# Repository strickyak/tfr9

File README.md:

# tfr9

The TFR/9 Single Board Computer for Hitachi 6309E or Motorola 6809E CPUs (TFR/901)

This represents one approach to mixing retro computers with modern
attachments: The CPU will be genuine retro, a 6809E or 6309E from the
era, but all the other parts are replaced by a Raspberry Pi Picos,
including the RAM and the E/Q clock generation.

The hope is to make very affordable Single Board Computers running
Nitros-9 Level 1 or 2 OS, since a 6309 is under $5, a Pi Pico is around $5.

(Another board taking this kind of modern-retro approach is the Olimex Neo6502
which sells for around 30 Euro.)

## TFR/905h

Finished, tested boards can be ordered (or soon can be ordered) from
https://computerconect.com/collections/coco-hardware

Here is the Hardware Reference Manual:
https://github.com/strickyak/tfr9/wiki/TFR-905-Hardware-Reference

Here is the latest software:
https://github.com/strickyak/tfr9/tree/main/v3

Here are the Kicad design files, and Gerbers and CPL and BOM for
[JLCPCB](https://jlcpcb.com/) :
https://github.com/strickyak/tfr9/tree/main/tfr905h

It works best with a
[Hitachi HD63C09EP](https://www.ebay.com/itm/375885991013) and a
[Pi Pico 2](https://www.digikey.com/en/products/detail/raspberry-pi/SC1631/24627136)
(and those links are where I got my parts from).

The design goals of the 905h were
 
* Cheap. Two layer, 100mm x 100mm, common parts.

* Works with all Pi Picos {1, 1w, 2, 2w}.

* Uses only 12 GPIO pins, from 0 to 11.

* That leaves plenty of GPIO lines free for audio, video,
interfacing, experimentation ... including all 8 HSTX (high
speed transmit) pins.

* All 40 pins on the 6309 and all 40 pins on the Pi Pico
can have headers attached, for easy interfacing.

* Powered and controlled over USB, by a program 
that runs on any modern PC (Windows, Mac, Linux, Pi).

* Anti-goals: Maybe not the fastest or the simplest
(but it's fast enough and simple enough).

## TFR/903 (obsolete)

This board should work with either 6809E or 6309E, but hereafter we'll
just call it the 6309, but we probably mean a Hitachi 63C09E.  The E is
important -- the CPU must be externally clocked.

We're starting with one Pico in the first prototype, but we might
add more:

* The first Pico is the controller.
  It provides clocks and simulates RAM (hopefully with MMU)
  and a terminal device.  Probably also disk and ethernet.

* A second Pico can generate video output.  This use of a Pico
  has been demonstrated several times, with VGA or DVI output,
  and even with an "HDMI connector".

* A third Pico could be a Pico W which does wifi internet.

## TFR/901 (2024-07-13) (obsolete)

The TFR/901 is the first prototype for the TFR/9 architecture.

It contains slots for a Hitachi 63C09E and one Raspberry Pi Pico, and just
enough multiplexing, latching, and voltage level shifting to connect them.

The hope is that the Pico can provide all the RAM and IO facilities
needed for the 6309/6809 CPU.  It also provides the E and Q clocks,
and there are connections for all inputs and outputs of the CPU chip.

Since this is for prototyping, there are optional header pins for all
interesting signals, and through-hole DIPs are used for all the chips.
There should be ample room to bodge stuff, if mistakes were made.

### First Pico

The first Pi Pico is the controller.  It has the ability to completely
control the 6309 CPU, as if the CPU lives suspended in the matrix.
And yet the 6309, and it alone, will do all the things you expect the
CPU to do.  It is not emulated or simulated, just controlled.

### First Pico Pins

GPIO pins G0 to G15 are a general purpose bidirectional bus.  What is
on this bus will depend on which Y mode is chosen, below.

GPIO pins 16 and 17 are output for the E and Q clock signals to the CPU,
These can be slowed down or sped up at the will of the Pi Pico.

G18, G19, and G20 are outputs to a 74138 3-to-8 decoder, which chooses
one of 8 modes, named Y0 to Y7.

Y0 does nothing.

Y1 maps CPU output Adddress lines A0-A15 to GPIO inputs G0 to G15.

Y2 maps CPU output Data lines D0-D7 to GPIO inputs G0 to G7, and also
various output signals R/W, AVMA, LIC, BUSY, BA, BS...  to GPIO inputs
in the range G8 to G15.

Y3 maps GPIO outputs G0 to G7 to CPU inputs D0-D7.

Y4 latches signals on G8 to G15 to various CPU inputs like RESET, HALT,
NMI, IRQ, FIRQ.   These are "slow" inputs that typically last more than
one CPU cycle, so they are latched, unlike the other signals above.

Y5, Y6, and Y7 will be trigger inputs to the second, third, etc, Pi
Picos, to send them data or receive data from them, over the G0 to G15
general bus.

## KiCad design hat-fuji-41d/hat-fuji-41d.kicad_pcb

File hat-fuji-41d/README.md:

# FujiNet Hat 41d

Works with Centipede 32z and the TFR/911h,
to provide FujiNet access.

Contains Bill Athing's fixes for the 40c,
and nary little more.

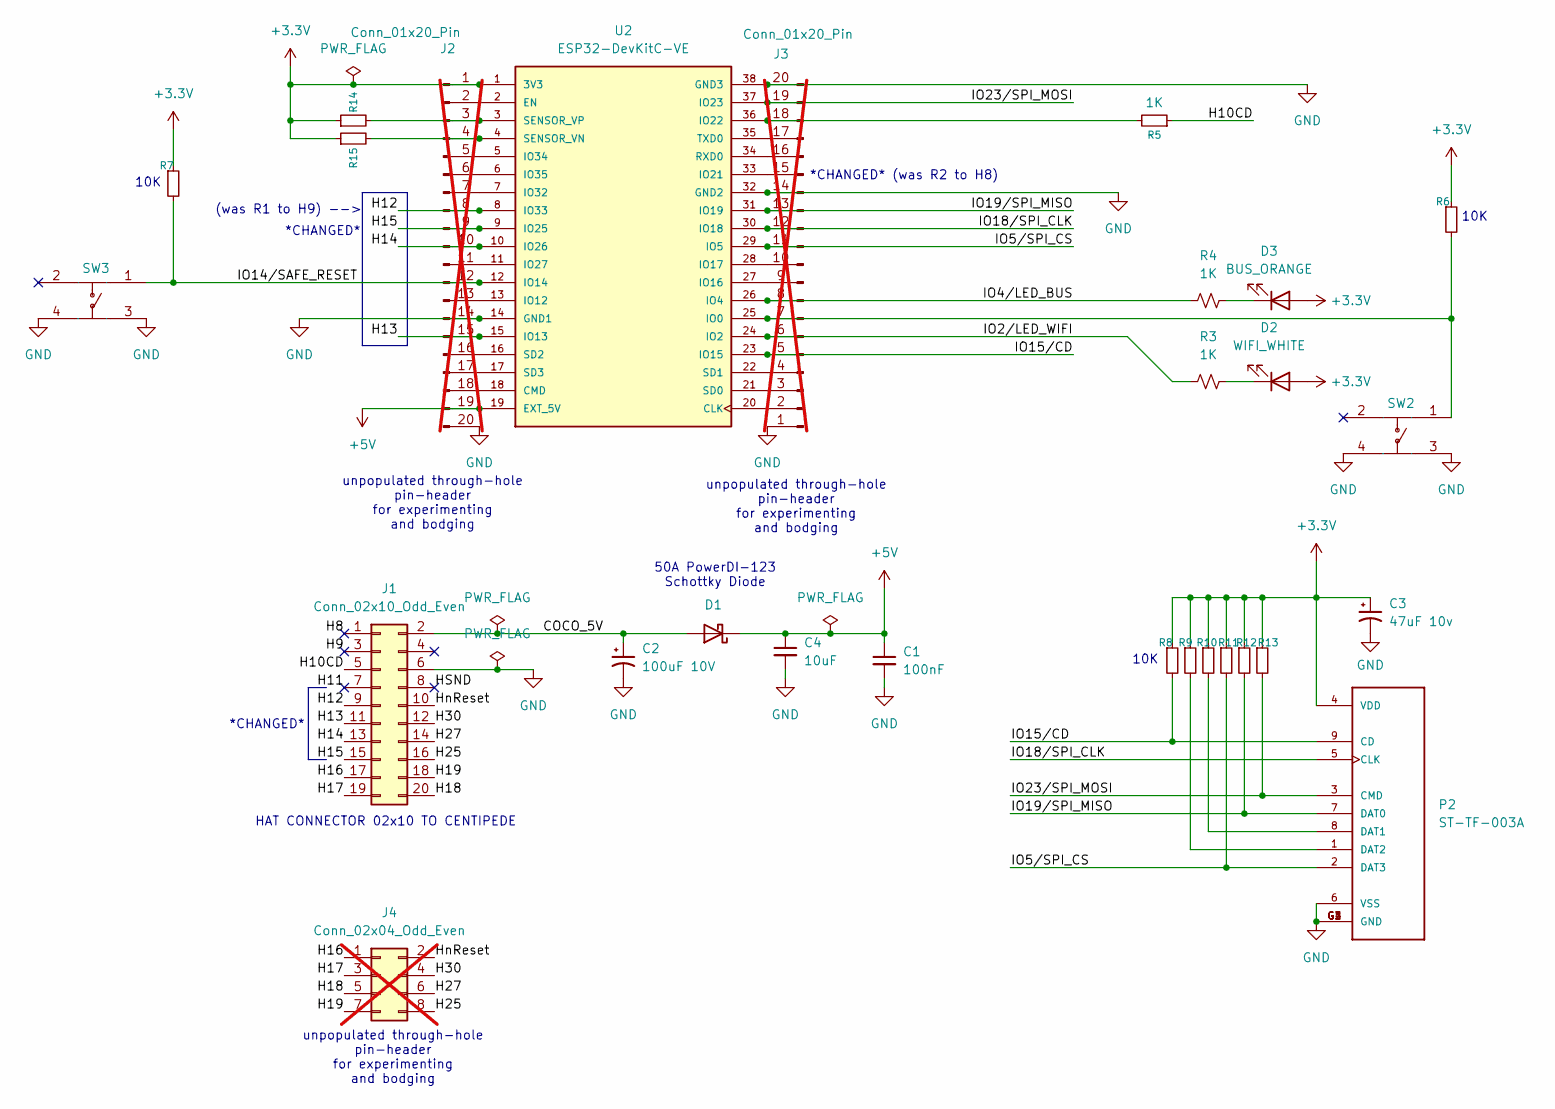
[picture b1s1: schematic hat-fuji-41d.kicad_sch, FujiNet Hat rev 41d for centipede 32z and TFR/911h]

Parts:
C1: 100nF; C_0402_1005Metric
C2: 100uF 10V; C_1206_3216Metric
C3: 47uF 10v; C_0805_2012Metric
C4: 10uF; C_0603_1608Metric
D1: 50A PowerDI-123 Schottky Diode; D_PowerDI-123
D2: WIFI_WHITE; LED_0603_1608Metric
D3: BUS_ORANGE; LED_0603_1608Metric
J1: Conn_02x10_Odd_Even; PinHeader_2x10_P2.54mm_Vertical_SMD
J2, J3: Conn_01x20_Pin; PinHeader_1x20_P2.54mm_Vertical; not fitted
J4: Conn_02x04_Odd_Even; PinHeader_2x04_P2.54mm_Vertical; not fitted
P2: ST-TF-003A; SUNTECH_ST-TF-003A
R3, R4, R5: 1K; R_0603_1608Metric
R6, R7, R8, R9, R10, R11, R12, R13, R14, R15: R_Small; R_0603_1608Metric
SW2, SW3: K2-1808SN-A4SW-01; KEY-SMD_4P-L4.2-W3.2-P2.20-LS5.1-TL; Manufacturer Part K2-1808SN-A4SW-01; LCSC Part Name 4.2mm*3.25mm
U2: ESP32-DevKitC-VE; MODULE_ESP32-DEVKITC-32U; PARTREV N/A

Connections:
+3.3V: C3.1, D2.2 (A), D3.2 (A), J2.1, P2.4 (VDD), R6.1, R7.1, R8.1, R9.1, R10.1, R11.1, R12.1, R13.1, R14.1, R15.1, U2.1 (3V3)
+5V: C1.1, C4.1, D1.1 (K), J2.19, U2.19 (EXT_5V)
/COCO_5V: C2.1, D1.2 (A), J1.2
/H8: J1.1
/H9: J1.3
/H10CD: J1.5, R5.1
/H11: J1.7
/H12: J1.9, J2.8, U2.8 (IO33)
/H13: J1.11, J2.15, U2.15 (IO13)
/H14: J1.13, J2.10, U2.10 (IO26)
/H15: J1.15, J2.9, U2.9 (IO25)
/H16: J1.17, J4.1
/H17: J1.19, J4.3
/H18: J1.20, J4.5
/H19: J1.18, J4.7
/H25: J1.16, J4.8
/H27: J1.14, J4.6
/H30: J1.12, J4.4
/HSND: J1.8
/HnReset: J1.10, J4.2
/IO2/LED_WIFI: J3.6, R3.2, U2.24 (IO2)
/IO4/LED_BUS: J3.8, R4.2, U2.26 (IO4)
/IO5/SPI_CS: J3.11, P2.2 (DAT3), R11.2, U2.29 (IO5)
/IO14/SAFE_RESET: J2.12, R7.2, SW3.1, U2.12 (IO14)
/IO15/CD: J3.5, P2.9 (CD), R8.2, U2.23 (IO15)
/IO18/SPI_CLK: J3.12, P2.5 (CLK), U2.30 (IO18)
/IO19/SPI_MISO: J3.13, P2.7 (DAT0), R12.2, U2.31 (IO19)
/IO23/SPI_MOSI: J3.19, P2.3 (CMD), R13.2, U2.37 (IO23)
GND: C1.2, C2.2, C3.2, C4.2, J1.6, J2.14, J2.20, J3.1, J3.14, J3.20, P2.6 (VSS), P2.G1 (GND), P2.G2 (GND), P2.G3 (GND), P2.G4 (GND), SW2.3, SW2.4, SW3.3, SW3.4, U2.14 (GND1), U2.32 (GND2), U2.38 (GND3)
unnamed: D2.1 (K), R3.1
unnamed: D3.1 (K), R4.1
unnamed: J2.2, U2.2 (EN)
unnamed: J2.3, R14.2, U2.3 (SENSOR_VP)
unnamed: J2.4, R15.2, U2.4 (SENSOR_VN)
unnamed: J2.5, U2.5 (IO34)
unnamed: J2.6, U2.6 (IO35)
unnamed: J2.7, U2.7 (IO32)
unnamed: J2.11, U2.11 (IO27)
unnamed: J2.13, U2.13 (IO12)
unnamed: J2.16, U2.16 (SD2)
unnamed: J2.17, U2.17 (SD3)
unnamed: J2.18, U2.18 (CMD)
unnamed: J3.2, U2.20 (CLK)
unnamed: J3.3, U2.21 (SD0)
unnamed: J3.4, U2.22 (SD1)
unnamed: J3.7, R6.2, SW2.1, U2.25 (IO0)
unnamed: J3.9, U2.27 (IO16)
unnamed: J3.10, U2.28 (IO17)
unnamed: J3.15, U2.33 (IO21)
unnamed: J3.16, U2.34 (RXD0)
unnamed: J3.17, U2.35 (TXD0)
unnamed: J3.18, R5.2, U2.36 (IO22)
unnamed: P2.8 (DAT1), R10.2
unnamed: P2.1 (DAT2), R9.2

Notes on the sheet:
50A PowerDI-123 Schottky Diode
10K
unpopulated through-hole pin-header for experimenting and bodging
*CHANGED*
HAT CONNECTOR 02x10 TO CENTIPEDE
*CHANGED* (was R2 to H8)
(was R1 to H9) -->

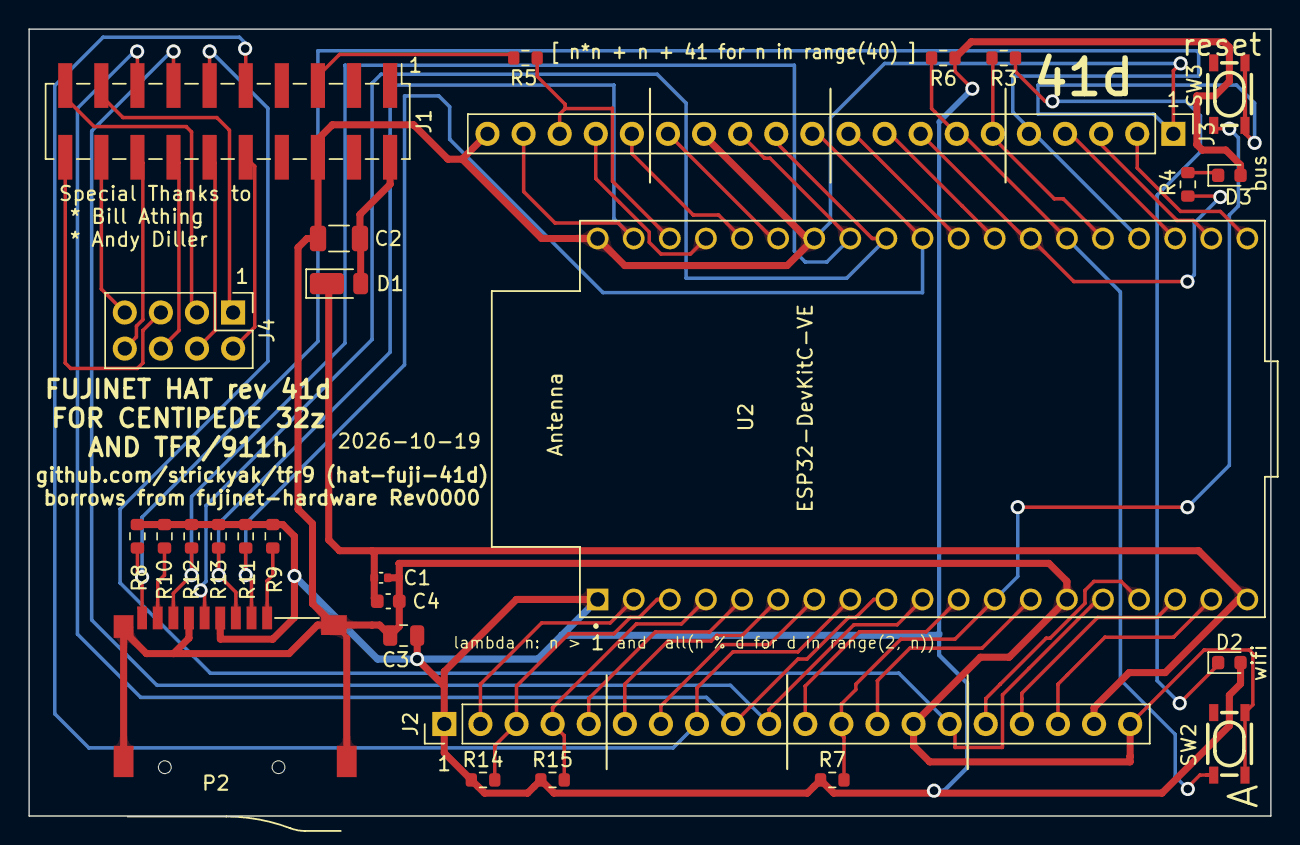
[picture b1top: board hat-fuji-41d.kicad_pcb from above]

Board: 2 copper layers, 87.4 x 55.4 mm, 28 parts (0 on the bottom side), 50 nets.

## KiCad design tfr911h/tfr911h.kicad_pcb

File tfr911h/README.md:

# RP2350B-Dev-Board

This is an RP2350B Dev board that breaks out all 48 GPIO pins.

It follows the original footprint of the RP2040 dev board, but adds 10 pins on each side.

It is not pin compatible with the original RP2040, though a version that shares the same pinout, at least for the first 20 pins on each side would be interesting.

Pinout:

```
1	GPIO0	        60	VBUS
2	GPIO1	        59	VSYS
3	GPIO2	        58	GND
4	GPIO3	        57	3v3
5	GPIO4	        56	3v3_EN
6	GPIO5	        55	ADC_VREF
7	GPIO6	        54	GND
8	GPIO7	        53	GPIO47/ADC7
9	GPIO8	        52	GPIO46/ADC6
10	GPIO9	        51	GPIO45/ADC5
11	GND	            50	GPIO44/ADC4
12	GPIO10	        49	GND
13	GPIO11	        48	GPIO43/ADC3
14	GPIO12	        47	GPIO42/ADC2
15	GPIO13	        46	GPIO41/ADC1
16	GPIO14	        45	GPIO40/ADC0
17	GPIO15	        44	GPIO39
18	GPIO16	        43	GPIO38
19	GPIO17	        42	GPIO37
20	GPIO18	        41	GPIO36
21	GPIO19	        40	GPIO35
22	GND	            39	GND
23	GPIO20	        38	GPIO34
24	GPIO21	        37	GPIO33
25	GPIO22	        36	GPIO32
26	GPIO23	        35	GPIO31
27	GPIO24	        34	GPIO30
28	GPIO25	        33	GPIO29
29	GPIO26	        32	GPIO28
30	GPIO27	        31	RUN
```

## Production files for JLCPCB

The production files for JLCPCB are in the 'production' directory.

RP2350_Dev_board.zip is the zipped Gerber files.

bom.csv and positions.csv are the Bill of materials and placements files respectively.

These were produced with the 'Fabrication Toolkit' plugin, which you will need to install if you need to regenerate them.

## Source Designs

Thie design borrows from https://pro.easyeda.com/editor#id=a0a21c97b13d436db5579fc2a8b1625d, which is an RP2350A design. I adapted it for the RP2350B, but it shares most of the schematic, if not the PCB layout.

I also looked at the RP2350B reference designs available here: https://datasheets.raspberrypi.com/rp2350/Minimal-KiCAD.zip

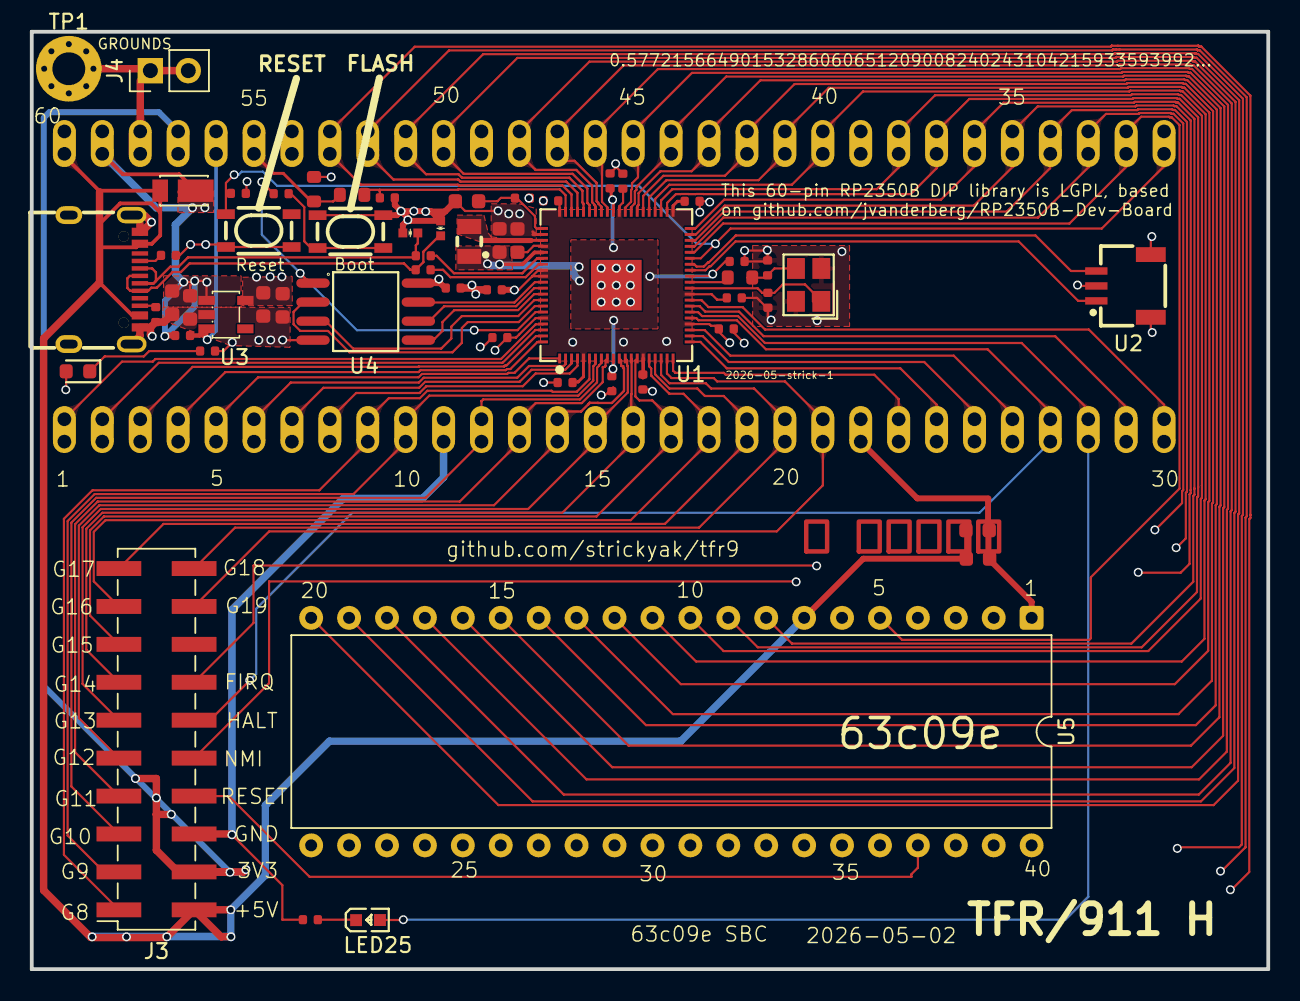
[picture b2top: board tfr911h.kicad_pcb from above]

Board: 4 copper layers, 82.8 x 62.8 mm, 116 parts (0 on the bottom side), 79 nets.

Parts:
3V3_EN1, 3V31: Castellated Pad
ADC_VREF1: Castellated Pad
Boot1: K2-1808SN-A4SW-01; KEY-SMD_4P-L4.2-W3.2-P2.20-LS5.1-TL
C1, C2, C3, C4, C5, C6, C7, C8, C9, C13, C14, C15, C16, C36: 100nF; C_0402
C10, C11, C12: 4.7uF; C_0603
C17, C18: 15pF; C_0402
C19: 4.7uF; C_0402
C20, C37, C40: 10uF; C_0603
C21, C38, C39: 100nF; C_0603
D1: POWERDI-123_L2.8-W1.8-LS3.7-RD
D2, D3: RCLAMP0521P.TCT-MS; D0402-BI
GND1, GND2, GND3, GND4, GND4#2, GND6: Castellated Pad
GPI10: Castellated Pad
GPIO0, GPIO1, GPIO1#2, GPIO1#3, GPIO1#4, GPIO1#5, GPIO1#6, GPIO1#7, GPIO1#8, GPIO2, GPIO3, GPIO4, GPIO5, GPIO7, GPIO8, GPIO11, GPIO12, GPIO13, GPIO15, GPIO16, GPIO17, GPIO18, GPIO19, GPIO21, GPIO21#2, GPIO22, GPIO24, GPIO25, GPIO26, GPIO27, GPIO28, GPIO29, GPIO30, GPIO32, GPIO34, GPIO35, GPIO36, GPIO37, GPIO38, GPIO39, GPIO40, GPIO41, GPIO42, GPIO43, GPIO44, GPIO45, GPIO46: Castellated Pad
J3: Conn_02x10_Odd_Even; PinSocket_2x10_P2.54mm_Vertical_SMD
J4: Conn_01x02; PinHeader_1x02_P2.54mm_Vertical
L1: IND-SMD_L2.0-W1.6_AOTA-B201610S3R3-101-T
LED25: Red; LED0603-RD_RED
PWR_LED1: Red; D_0603
R1, R4: 5.1kΩ; R_0402
R2, R3, R6: 33Ω; R_0402
R5: 1kΩ; R_0402
R7: 1Ω; R_0603
R8: 200Ω; R_0603
R9: 5kΩ; R_0402
R11: 100kΩ; R_0402
R12: 2kΩ; R_0402
R28: 1kΩ; R_0603
RUN1: Castellated Pad
Reset1: K2-1808SN-A4SW-01; KEY-SMD_4P-L4.2-W3.2-P2.20-LS5.1-TL
TP1: TestPoint_Alt; MountingHole_2.2mm_M2_Pad_Via
U1: QFN-80_L10.0-W10.0-P0.40-TL-EP3.4
U2: HC-1.0-3PWT; CONN-SMD_3P-P1.0-HC-1.0-3PWT
U3: SOT-23-5_L3.0-W1.7-P0.95-LS2.8-BR
U4: W25Q128; SOIC-8_L5.3-W5.3-P1.27-LS8.0-BL
U5: MC6809E; DIP-40_W15.24mm
USB1: USB-C-SMD_TYPE-C-6PIN-2MD-073
VBUS1: Castellated Pad
VSYS1: Castellated Pad
X1: CRYSTAL-SMD_4P-L3.2-W2.5-BL

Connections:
1V1: C2.1, C5.1, C10.2, C13.2, L1.2, U1.10 (DVDD), U1.32 (DVDD), U1.51 (DVDD), U1.65 (VREG_FB)
3V3: 3V31.57, C1.1, C3.1, C4.1, C6.1, C7.1, C8.2, C9.2, C12.2, C14.2, C16.2, C36.2, C38.1, C40.1, J3.4, PWR_LED1.2, R6.1, R8.2, U1.5 (IOVDD), U1.15 (IOVDD), U1.24 (IOVDD), U1.29 (IOVDD), U1.41 (IOVDD), U1.50 (IOVDD), U1.60 (IOVDD), U1.64 (VREG_VIN), U1.68 (USB_OTP_VDD), U1.69 (QSPI_IOVDD), U1.76 (IOVDD), U3.5 (VOUT), U4.8 (VCC)
3V3_EN: 3V3_EN1.56, R11.2, U3.3 (CE)
/VREG_LX: L1.1, U1.63 (VREG_LX)
ADC_VREF: ADC_VREF1.55, R7.2, R8.1
GND: Boot1.3, Boot1.4, C1.2, C2.2, C3.2, C4.2, C5.2, C6.2, C7.2, C8.1, C9.1, C10.1, C11.1, C12.1, C13.1, C14.1, C15.1, C16.1, C17.2, C18.1, C19.2, C20.2, C21.2, C36.1, C37.2, C38.2, C39.2, C40.2, D2.1, D3.1, GND2.22, GND3.39, GND4.49, GND4#2.54, GND6.58, GPI10.11, J3.6, J4.1, J4.2, R1.1, R4.1, R9.2, R12.2, Reset1.3, Reset1.4, TP1.1, U1.62 (VREG_PGND), U1.81 (GND), U2.2, U2.4, U2.5, U3.2 (VSS), U4.4 (GND), U5.1 (VSS), U5.39 (TSC), USB1.1 (GND), USB1.12 (GND), USB1.13 (SHELL), USB1.14 (SHELL), X1.2 (GND), X1.4 (GND)
GPIO0: GPIO0.1, U1.77 (GPIO0), U5.31 (D0)
GPIO1: GPIO1#2.2, U1.78 (GPIO1), U5.30 (D1)
GPIO2: GPIO2.3, U1.79 (GPIO2), U5.29 (D2)
GPIO3: GPIO3.4, U1.80 (GPIO3), U5.28 (D3)
GPIO4: GPIO4.5, U1.1 (GPIO4), U5.27 (D4)
GPIO5: GPIO5.6, U1.2 (GPIO5), U5.26 (D5)
GPIO6: GPIO1#8.7, U1.3 (GPIO6), U5.25 (D6)
GPIO7: GPIO7.8, U1.4 (GPIO7), U5.24 (D7)
GPIO8: GPIO8.9, J3.1, U1.6 (GPIO8)
GPIO9: GPIO1#7.10, J3.3, U1.7 (GPIO9)
GPIO10: GND1.12, J3.5, U1.8 (GPIO10)
GPIO11: GPIO11.13, J3.7, U1.9 (GPIO11)
GPIO12: GPIO12.14, J3.9, U1.11 (GPIO12)
GPIO13: GPIO13.15, J3.11, U1.12 (GPIO13)
GPIO14: GPIO1#6.16, J3.13, U1.13 (GPIO14)
GPIO15: GPIO15.17, J3.15, U1.14 (GPIO15)
GPIO16: GPIO16.18, J3.17, U1.16 (GPIO16)
GPIO17: GPIO17.19, J3.19, U1.17 (GPIO17)
GPIO18: GPIO18.20, J3.20, U1.18 (GPIO18)
GPIO19: GPIO19.21, J3.18, U1.19 (GPIO19)
GPIO20: GPIO21.23, J3.8, U1.20 (GPIO20), U5.37 (~RESET)
GPIO21: GPIO21#2.24, J3.10, U1.21 (GPIO21), U5.2 (~NMI)
GPIO22: GPIO22.25, U1.22 (GPIO22), U5.3 (~IRQ)
GPIO23: GPIO1#5.26, J3.14, U1.23 (GPIO23), U5.4 (~FIRQ)
GPIO24: GPIO24.27, J3.12, U1.25 (GPIO24), U5.40 (~HALT)
GPIO25: GPIO25.28, LED25.2, U1.26 (GPIO25)
GPIO26: GPIO26.29, U1.27 (GPIO26), U5.38 (LIC)
GPIO27: GPIO27.30, U1.28 (GPIO27), U5.36 (AVMA)
GPIO28: GPIO28.31, U1.36 (GPIO28), U5.5 (BS)
GPIO29: GPIO29.33, U1.37 (GPIO29), U5.34 (E)
GPIO30: GPIO30.34, U1.38 (GPIO30), U5.35 (Q)
GPIO31: GPIO1#4.1, GPIO1#4.35, U1.39 (GPIO31), U5.32 (R/~W)
GPIO32: GPIO1.36, U1.40 (GPIO32), U5.8 (A0)
GPIO33: GPIO32.37, U1.42 (GPIO33), U5.9 (A1)
GPIO34: GPIO34.38, U1.43 (GPIO34), U5.10 (A2)
GPIO35: GPIO35.40, U1.44 (GPIO35), U5.11 (A3)
GPIO36: GPIO36.41, U1.45 (GPIO36), U5.12 (A4)
GPIO37: GPIO37.42, U1.46 (GPIO37), U5.13 (A5)
GPIO38: GPIO38.43, U1.47 (GPIO38), U5.14 (A6)
GPIO39: GPIO39.44, U1.48 (GPIO39), U5.15 (A7)
GPIO40/ADC0: GPIO40.45, U1.49 (GPIO40_ADC0), U5.16 (A8)
GPIO41/ADC1: GPIO41.46, U1.52 (GPIO41_ADC1), U5.17 (A9)
GPIO42/ADC2: GPIO42.47, U1.53 (GPIO42_ADC2), U5.18 (A10)
GPIO43/ADC3: GPIO43.48, U1.54 (GPIO43_ADC3), U5.19 (A11)
GPIO44/ADC4: GPIO44.50, U1.55 (GPIO44_ADC4), U5.20 (A12)
GPIO45/ADC5: GPIO45.51, U1.56 (GPIO45_ADC5), U5.21 (A13)
GPIO46/ADC6: GPIO46.52, U1.57 (GPIO46_ADC6), U5.22 (A14)
GPIO47/ADC7: GPIO1#3.53, U1.58 (GPIO47_ADC7), U5.23 (A15)
unnamed: Boot1.1, Boot1.2, R5.1
unnamed: C17.1, R28.1, X1.3
unnamed: LED25.1, R9.1
unnamed: PWR_LED1.1, R12.1
unnamed: C19.1, R7.1, U1.59 (ADC_AVDD)
unnamed: U1.71 (QSPI_SCLK), U4.6 (CLK)
unnamed: U1.72 (QSPI_SD0), U4.5 (DI)
unnamed: U1.74 (QSPI_SD1), U4.2 (DO)
unnamed: U1.73 (QSPI_SD2), U4.3 (IO2)
unnamed: U1.70 (QSPI_SD3), U4.7 (IO3)
unnamed: R5.2, U1.75 (QSPI_SS), U4.1 (CS#)
unnamed: U1.33 (SWCLK), U2.1
unnamed: U1.34 (SWDIO), U2.3
unnamed: R2.1, U1.66 (USB_DM)
unnamed: R3.1, U1.67 (USB_DP)
unnamed: C11.2, R6.2, U1.61 (VREG_AVDD)
unnamed: C18.2, U1.30 (XIN), X1.1
unnamed: R28.2, U1.31 (XOUT)
unnamed: R1.2, USB1.4 (CC1)
unnamed: R4.2, USB1.10 (CC2)
RUN: C15.2, RUN1.30, Reset1.1, U1.35 (RUN)
USB2_D+: D3.2, R3.2, USB1.6 (DP1), USB1.8 (DP2)
USB2_D-: D2.2, R2.2, USB1.5 (DN2), USB1.7 (DN1)
VBUS: C20.1, C21.1, D1.2, J3.2, U5.7 (VCC), USB1.2 (VBUS), USB1.11 (VBUS), VBUS1.60
VSYS: C37.1, C39.1, D1.1, R11.1, U3.1 (VIN), VSYS1.59

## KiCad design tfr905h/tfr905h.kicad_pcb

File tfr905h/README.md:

# TFR/905

The goals of this board

*   Cheap 2-layer 100x100mm board.

*   Just one Pi Pico; can be any of

    1) Pi Pico
    1) Pi Pico W
    1) Pi Pico 2
    1) Pi Pico 2 W

*   Free up many GPIO pins: GPIO 12-22 and 26-28 are available.

*   Those include the HSTX (high speed trasmit) pins, for video output.

The multiplexing buffer control is a bit different now.

The TFR/901 had GPIO 3 outputs to a '138 3-to-8 decoder to control the 3-state buffers.

The TFR/903 had GPIO outputs direct to the buffers.

Now we have a 3-bit counter feeding a '138,
so only 2 GPIO lines are required to 1. reset and 2. increment the counter
to control the buffers.

So there is an 8-bit bus on GPIO 0-7.

And only four side outputs: E, Q, CounterReset and CounterIncrement.

NOTICE: tfr905g had one error, fixed on tfr905h (OE of U2).

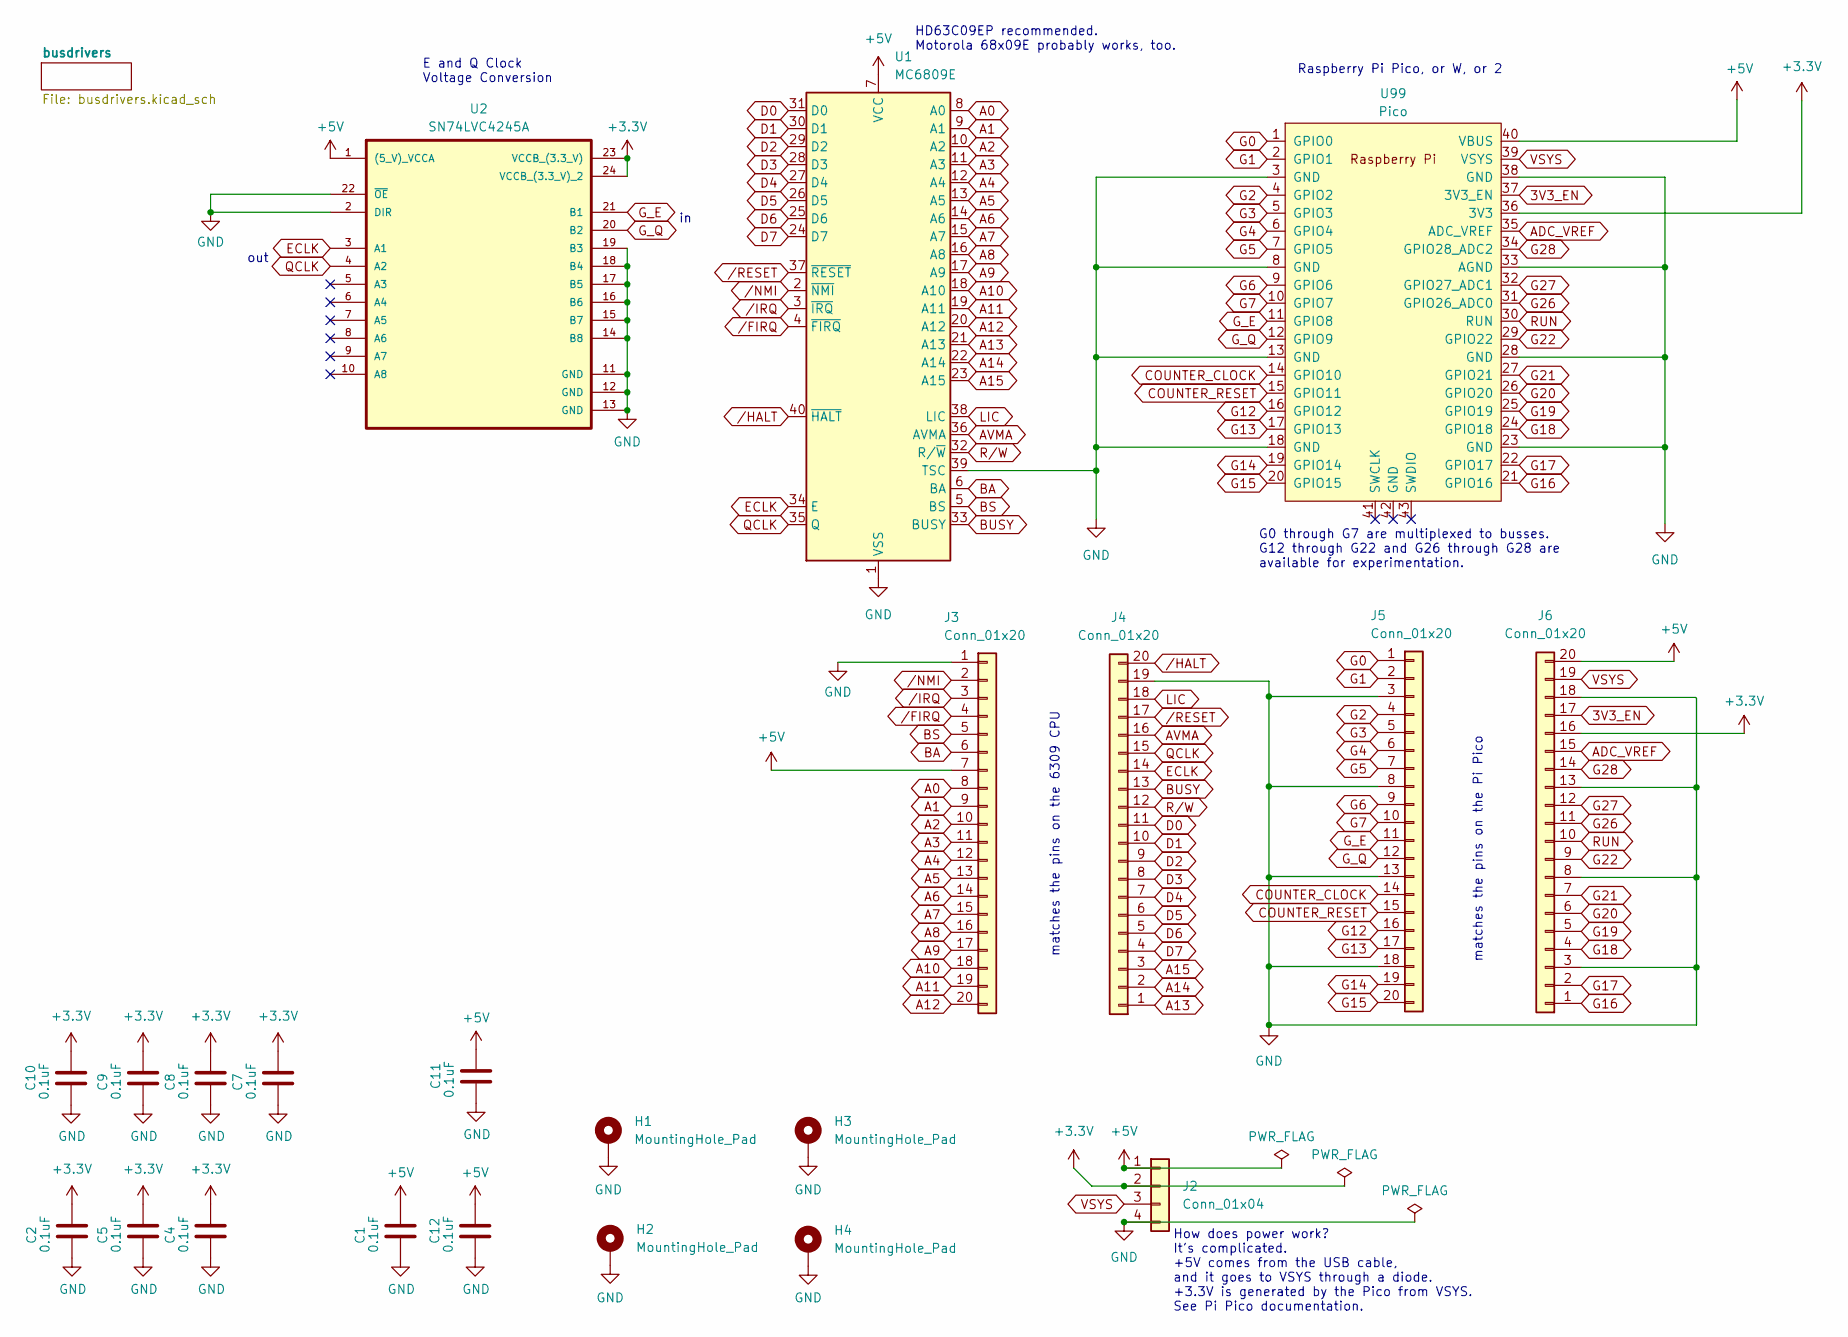
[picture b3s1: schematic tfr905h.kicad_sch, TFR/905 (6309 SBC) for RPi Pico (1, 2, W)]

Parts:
C1, C2, C4, C5, C7, C8, C9, C10, C11, C12: 0.1uF; C_0402_1005Metric
H1, H2, H3, H4: MountingHole_Pad; TestPoint_Plated_Hole_D4.0mm
J2: Conn_01x04; PinHeader_1x04_P2.54mm_Vertical
J3, J4, J5, J6: Conn_01x20; PinHeader_1x20_P2.54mm_Vertical
U1: MC6809E; DIP-40_W15.24mm
U2: SN74LVC4245A; TSSOP-24_4.4x7.8mm_P0.65mm
U99: Pico; RPi_PicoW_SMD_TH

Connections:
3V3_EN: J6.17, U99.37 (3V3_EN)
+3.3V: C2.1, C4.1, C5.1, C7.1, C8.1, C9.1, C10.1, J2.2, J6.16, U2.23 (VCCB_(3.3_V)), U2.24 (VCCB_(3.3_V)_2), U99.36 (3V3); also elsewhere on the board
+5V: C1.1, C11.1, C12.1, J2.1, J3.7, J6.20, U1.7 (VCC), U2.1 ((5_V)_VCCA), U99.40 (VBUS); also elsewhere on the board
A0: J3.8, U1.8 (A0); also elsewhere on the board
A1: J3.9, U1.9 (A1); also elsewhere on the board
A2: J3.10, U1.10 (A2); also elsewhere on the board
A3: J3.11, U1.11 (A3); also elsewhere on the board
A4: J3.12, U1.12 (A4); also elsewhere on the board
A5: J3.13, U1.13 (A5); also elsewhere on the board
A6: J3.14, U1.14 (A6); also elsewhere on the board
A7: J3.15, U1.15 (A7); also elsewhere on the board
A8: J3.16, U1.16 (A8); also elsewhere on the board
A9: J3.17, U1.17 (A9); also elsewhere on the board
A10: J3.18, U1.18 (A10); also elsewhere on the board
A11: J3.19, U1.19 (A11); also elsewhere on the board
A12: J3.20, U1.20 (A12); also elsewhere on the board
A13: J4.1, U1.21 (A13); also elsewhere on the board
A14: J4.2, U1.22 (A14); also elsewhere on the board
A15: J4.3, U1.23 (A15); also elsewhere on the board
ADC_VREF: J6.15, U99.35 (ADC_VREF)
AVMA: J4.16, U1.36 (AVMA); also elsewhere on the board
BA: J3.6, U1.6 (BA); also elsewhere on the board
BS: J3.5, U1.5 (BS); also elsewhere on the board
BUSY: J4.13, U1.33 (BUSY); also elsewhere on the board
COUNTER_CLOCK: J5.14, U99.14 (GPIO10); also elsewhere on the board
COUNTER_RESET: J5.15, U99.15 (GPIO11); also elsewhere on the board
D0: J4.11, U1.31 (D0); also elsewhere on the board
D1: J4.10, U1.30 (D1); also elsewhere on the board
D2: J4.9, U1.29 (D2); also elsewhere on the board
D3: J4.8, U1.28 (D3); also elsewhere on the board
D4: J4.7, U1.27 (D4); also elsewhere on the board
D5: J4.6, U1.26 (D5); also elsewhere on the board
D6: J4.5, U1.25 (D6); also elsewhere on the board
D7: J4.4, U1.24 (D7); also elsewhere on the board
ECLK: J4.14, U1.34 (E), U2.3 (A1)
G0: J5.1, U99.1 (GPIO0); also elsewhere on the board
G1: J5.2, U99.2 (GPIO1); also elsewhere on the board
G2: J5.4, U99.4 (GPIO2); also elsewhere on the board
G3: J5.5, U99.5 (GPIO3); also elsewhere on the board
G4: J5.6, U99.6 (GPIO4); also elsewhere on the board
G5: J5.7, U99.7 (GPIO5); also elsewhere on the board
G6: J5.9, U99.9 (GPIO6); also elsewhere on the board
G7: J5.10, U99.10 (GPIO7); also elsewhere on the board
G12: J5.16, U99.16 (GPIO12)
G13: J5.17, U99.17 (GPIO13)
G14: J5.19, U99.19 (GPIO14)
G15: J5.20, U99.20 (GPIO15)
G16: J6.1, U99.21 (GPIO16)
G17: J6.2, U99.22 (GPIO17)
G18: J6.4, U99.24 (GPIO18)
G19: J6.5, U99.25 (GPIO19)
G20: J6.6, U99.26 (GPIO20)
G21: J6.7, U99.27 (GPIO21)
G22: J6.9, U99.29 (GPIO22)
G26: J6.11, U99.31 (GPIO26_ADC0)
G27: J6.12, U99.32 (GPIO27_ADC1)
G28: J6.14, U99.34 (GPIO28_ADC2)
GND: C1.2, C2.2, C4.2, C5.2, C7.2, C8.2, C9.2, C10.2, C11.2, C12.2, H1.1, H2.1, H3.1, H4.1, J2.4, J3.1, J4.19, J5.3, J5.8, J5.13, J5.18, J6.3, J6.8, J6.13, J6.18, U1.1 (VSS), U1.39 (TSC), U2.2 (DIR), U2.11 (GND), U2.12 (GND), U2.13 (GND), U2.14 (B8), U2.15 (B7), U2.16 (B6), U2.17 (B5), U2.18 (B4), U2.19 (B3), U2.22 (~OE), U99.3 (GND), U99.8 (GND), U99.13 (GND), U99.18 (GND), U99.23 (GND), U99.28 (GND), U99.33 (AGND), U99.38 (GND); also elsewhere on the board
G_E: J5.11, U2.21 (B1), U99.11 (GPIO8)
G_Q: J5.12, U2.20 (B2), U99.12 (GPIO9)
LIC: J4.18, U1.38 (LIC); also elsewhere on the board
QCLK: J4.15, U1.35 (Q), U2.4 (A2)
RUN: J6.10, U99.30 (RUN)
R/W: J4.12, U1.32 (R/~W); also elsewhere on the board
VSYS: J2.3, J6.19, U99.39 (VSYS)
/FIRQ: J3.4, U1.4 (~FIRQ); also elsewhere on the board
/HALT: J4.20, U1.40 (~HALT); also elsewhere on the board
/IRQ: J3.3, U1.3 (~IRQ); also elsewhere on the board
/NMI: J3.2, U1.2 (~NMI); also elsewhere on the board
/RESET: J4.17, U1.37 (~RESET); also elsewhere on the board

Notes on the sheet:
Raspberry Pi Pico, or W, or 2
How does power work? It's complicated. +5V comes from the USB cable, and it goes to VSYS through a diode. +3.3V is generated by the Pico from VSYS. See Pi Pico documentation.
matches the pins on the Pi Pico
HD63C09EP recommended. Motorola 68x09E probably works, too.
matches the pins on the 6309 CPU
out
E and Q Clock Voltage Conversion
G0 through G7 are multiplexed to busses. G12 through G22 and G26 through G28 are available for experimentation.

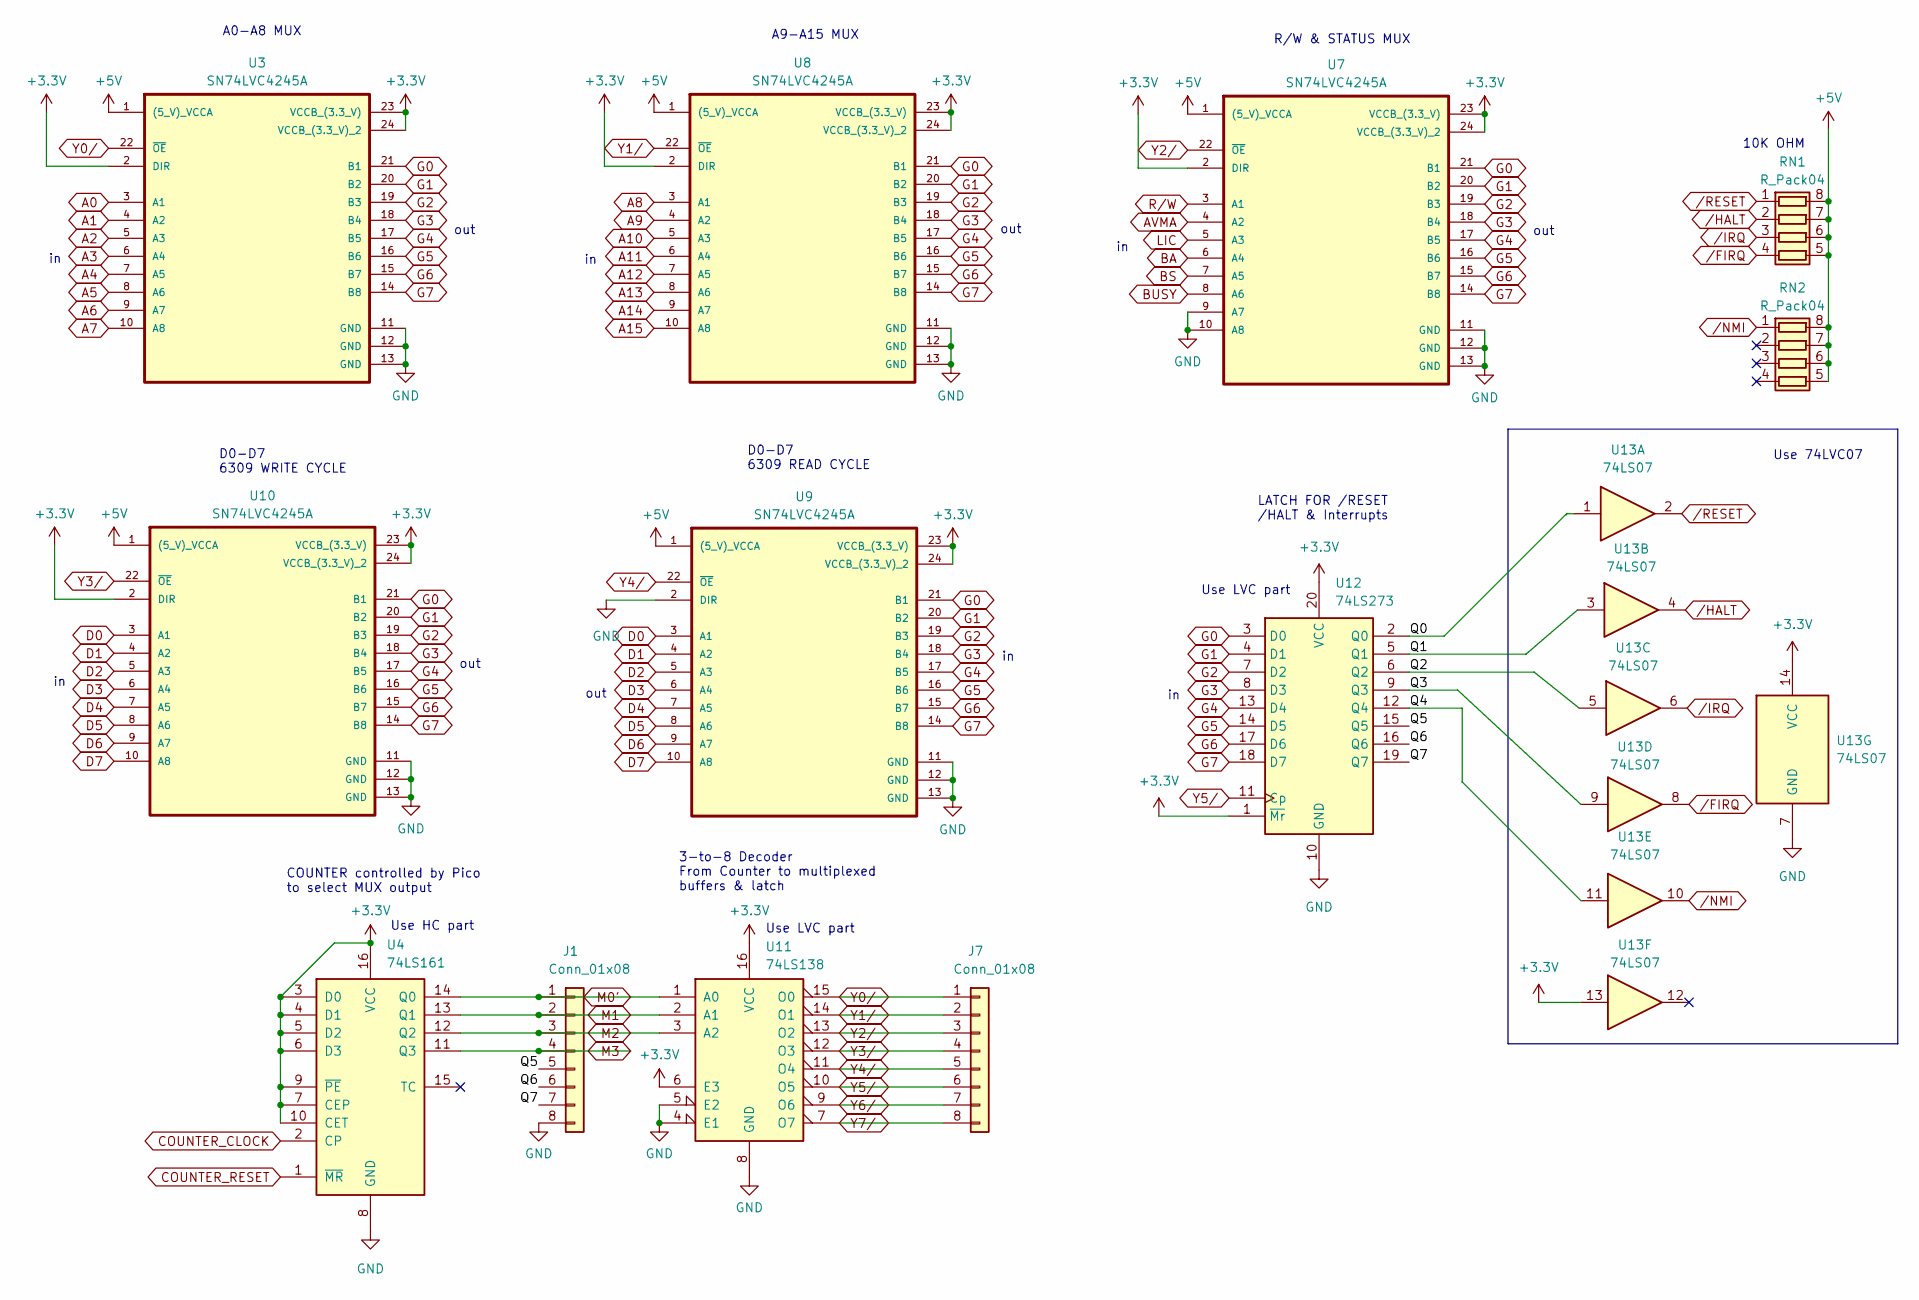
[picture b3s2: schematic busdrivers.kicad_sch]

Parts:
J1, J7: Conn_01x08; PinHeader_1x08_P2.54mm_Vertical
RN1, RN2: R_Pack04; R_Array_Concave_4x0603
U3, U7, U8, U9, U10: SN74LVC4245A; TSSOP-24_4.4x7.8mm_P0.65mm
U4: 74LS161; SOIC-16_3.9x9.9mm_P1.27mm
U11: 74LS138; SOIC-16_3.9x9.9mm_P1.27mm
U12: 74LS273; TSSOP-20_4.4x6.5mm_P0.65mm
U13: 74LS07; SOIC-14_3.9x8.7mm_P1.27mm

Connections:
+3.3V: U3.2 (DIR), U3.23 (VCCB_(3.3_V)), U3.24 (VCCB_(3.3_V)_2), U4.3 (D0), U4.4 (D1), U4.5 (D2), U4.6 (D3), U4.7 (CEP), U4.9 (~PE), U4.10 (CET), U4.16 (VCC), U7.2 (DIR), U7.23 (VCCB_(3.3_V)), U7.24 (VCCB_(3.3_V)_2), U8.2 (DIR), U8.23 (VCCB_(3.3_V)), U8.24 (VCCB_(3.3_V)_2), U9.23 (VCCB_(3.3_V)), U9.24 (VCCB_(3.3_V)_2), U10.2 (DIR), U10.23 (VCCB_(3.3_V)), U10.24 (VCCB_(3.3_V)_2), U11.6 (E3), U11.16 (VCC), U12.1 (~Mr), U12.20 (VCC), U13.13, U13.14 (VCC); also elsewhere on the board
+5V: RN1.5 (R4.2), RN1.6 (R3.2), RN1.7 (R2.2), RN1.8 (R1.2), RN2.5 (R4.2), RN2.6 (R3.2), RN2.7 (R2.2), RN2.8 (R1.2), U3.1 ((5_V)_VCCA), U7.1 ((5_V)_VCCA), U8.1 ((5_V)_VCCA), U9.1 ((5_V)_VCCA), U10.1 ((5_V)_VCCA); also elsewhere on the board
/busdrivers/Q0: U12.2 (Q0), U13.1
/busdrivers/Q1: U12.5 (Q1), U13.3
/busdrivers/Q2: U12.6 (Q2), U13.5
/busdrivers/Q3: U12.9 (Q3), U13.9
/busdrivers/Q4: U12.12 (Q4), U13.11
/busdrivers/Q5: J1.5, U12.15 (Q5)
/busdrivers/Q6: J1.6, U12.16 (Q6)
/busdrivers/Q7: J1.7, U12.19 (Q7)
A0: U3.3 (A1); also elsewhere on the board
A1: U3.4 (A2); also elsewhere on the board
A2: U3.5 (A3); also elsewhere on the board
A3: U3.6 (A4); also elsewhere on the board
A4: U3.7 (A5); also elsewhere on the board
A5: U3.8 (A6); also elsewhere on the board
A6: U3.9 (A7); also elsewhere on the board
A7: U3.10 (A8); also elsewhere on the board
A8: U8.3 (A1); also elsewhere on the board
A9: U8.4 (A2); also elsewhere on the board
A10: U8.5 (A3); also elsewhere on the board
A11: U8.6 (A4); also elsewhere on the board
A12: U8.7 (A5); also elsewhere on the board
A13: U8.8 (A6); also elsewhere on the board
A14: U8.9 (A7); also elsewhere on the board
A15: U8.10 (A8); also elsewhere on the board
AVMA: U7.4 (A2); also elsewhere on the board
BA: U7.6 (A4); also elsewhere on the board
BS: U7.7 (A5); also elsewhere on the board
BUSY: U7.8 (A6); also elsewhere on the board
COUNTER_CLOCK: U4.2 (CP); also elsewhere on the board
COUNTER_RESET: U4.1 (~MR); also elsewhere on the board
D0: U9.3 (A1), U10.3 (A1); also elsewhere on the board
D1: U9.4 (A2), U10.4 (A2); also elsewhere on the board
D2: U9.5 (A3), U10.5 (A3); also elsewhere on the board
D3: U9.6 (A4), U10.6 (A4); also elsewhere on the board
D4: U9.7 (A5), U10.7 (A5); also elsewhere on the board
D5: U9.8 (A6), U10.8 (A6); also elsewhere on the board
D6: U9.9 (A7), U10.9 (A7); also elsewhere on the board
D7: U9.10 (A8), U10.10 (A8); also elsewhere on the board
G0: U3.21 (B1), U7.21 (B1), U8.21 (B1), U9.21 (B1), U10.21 (B1), U12.3 (D0); also elsewhere on the board
G1: U3.20 (B2), U7.20 (B2), U8.20 (B2), U9.20 (B2), U10.20 (B2), U12.4 (D1); also elsewhere on the board
G2: U3.19 (B3), U7.19 (B3), U8.19 (B3), U9.19 (B3), U10.19 (B3), U12.7 (D2); also elsewhere on the board
G3: U3.18 (B4), U7.18 (B4), U8.18 (B4), U9.18 (B4), U10.18 (B4), U12.8 (D3); also elsewhere on the board
G4: U3.17 (B5), U7.17 (B5), U8.17 (B5), U9.17 (B5), U10.17 (B5), U12.13 (D4); also elsewhere on the board
G5: U3.16 (B6), U7.16 (B6), U8.16 (B6), U9.16 (B6), U10.16 (B6), U12.14 (D5); also elsewhere on the board
G6: U3.15 (B7), U7.15 (B7), U8.15 (B7), U9.15 (B7), U10.15 (B7), U12.17 (D6); also elsewhere on the board
G7: U3.14 (B8), U7.14 (B8), U8.14 (B8), U9.14 (B8), U10.14 (B8), U12.18 (D7); also elsewhere on the board
GND: J1.8, U3.11 (GND), U3.12 (GND), U3.13 (GND), U4.8 (GND), U7.9 (A7), U7.10 (A8), U7.11 (GND), U7.12 (GND), U7.13 (GND), U8.11 (GND), U8.12 (GND), U8.13 (GND), U9.2 (DIR), U9.11 (GND), U9.12 (GND), U9.13 (GND), U10.11 (GND), U10.12 (GND), U10.13 (GND), U11.4 (E1), U11.5 (E2), U11.8 (GND), U12.10 (GND), U13.7 (GND); also elsewhere on the board
LIC: U7.5 (A3); also elsewhere on the board
M0': J1.1, U4.14 (Q0), U11.1 (A0)
M1: J1.2, U4.13 (Q1), U11.2 (A1)
M2: J1.3, U4.12 (Q2), U11.3 (A2)
M3: J1.4, U4.11 (Q3)
R/W: U7.3 (A1); also elsewhere on the board
Y0/: J7.1, U3.22 (~OE), U11.15 (O0)
Y1/: J7.2, U8.22 (~OE), U11.14 (O1)
Y2/: J7.3, U7.22 (~OE), U11.13 (O2)
Y3/: J7.4, U10.22 (~OE), U11.12 (O3)
Y4/: J7.5, U9.22 (~OE), U11.11 (O4)
Y5/: J7.6, U11.10 (O5), U12.11 (Cp)
Y6/: J7.7, U11.9 (O6)
Y7/: J7.8, U11.7 (O7)
/FIRQ: RN1.4 (R4.1), U13.8; also elsewhere on the board
/HALT: RN1.2 (R2.1), U13.4; also elsewhere on the board
/IRQ: RN1.3 (R3.1), U13.6; also elsewhere on the board
/NMI: RN2.1 (R1.1), U13.10; also elsewhere on the board
/RESET: RN1.1 (R1.1), U13.2; also elsewhere on the board

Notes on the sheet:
out
Use LVC part
A9-A15 MUX
COUNTER controlled by Pico to select MUX output
Use HC part
D0-D7 6309 READ CYCLE
D0-D7 6309 WRITE CYCLE
Use 74LVC07
3-to-8 Decoder From Counter to multiplexed buffers & latch
10K OHM
R/W & STATUS MUX
LATCH FOR /RESET /HALT & Interrupts
A0-A8 MUX

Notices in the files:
tfr901g/tfr901g.kicad_sch:
Released under the MIT License (opensource.org/license/mit)
tfr911h/tfr911h.kicad_pcb:
This 60-pin RP2350B DIP library is LGPL, based
